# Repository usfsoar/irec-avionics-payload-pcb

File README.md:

# IREC Avionics Payload PCB

This is the PCB for the payload of USF Society of Aeronautics and Rocketry's 2019 IREC rocket. The PCB is made in KiCad (pronounced key-cad). The different two parts of the payload are split into the folders ***payload_ground_pcb***, the ground station, and ***payload_main_pcb***, the cubesat payload, under those there are the files are:

* ***avionics-\*.pro*** - This is the base project which you should open in KiCad.
* ***avionics-\*.sch*** - This is the sketch of the PCB and shows which components should be connected where.
* ***avionics-\*.kicad_pcb*** - This is the actual PCB that has the components laid out and connected with physical dimensions.
* ***components*** - This folder contains components that are not by default included with KiCad

## About the board

The main components of the Cubesat Payload are:

* [Teensy 4.0](https://www.pjrc.com/store/teensy40.html) - This small Arduino compatible board is very powerful for its size with 600 MHz, 1M RAM, and 2M Flash as well as lots of connectivity options.
* [MS5607](https://www.te.com/commerce/DocumentDelivery/DDEController?Action=showdoc&DocId=Data+Sheet%7FMS5607-02BA03%7FB2%7Fpdf%7FEnglish%7FENG_DS_MS5607-02BA03_B2.pdf%7FCAT-BLPS0035) - This is the barometric sensor for the board, it provides high resolution and low pressure while being inexpensive and having a digital interface.
* [ADIS16470](https://www.analog.com/media/en/technical-documentation/data-sheets/ADIS16470.pdf) - This is the inertial measurement unit  which measures acceleration and direction. This highend component will provide an accurate and precice measurments and is the core of the payloads ability to be tracked in realtime by the ground station.
* [SAM M8Q](https://www.u-blox.com/sites/default/files/SAM-M8Q_DataSheet_%28UBX-16012619%29.pdf) - This is the GPS module and it provides a built in antenna and a digital interface.
* [RFM95W](https://cdn.sparkfun.com/assets/learn_tutorials/8/0/4/RFM95_96_97_98W.pdf) - For now this is a temporary RF module that will stand in for what ever RF solution is decided while testing. It provides many benefits for this purpose such as being in the 915MHz range and having long enough range that if necessary it could be used for launch.

The main components of the Ground Station are:

* Teensy 4.0
* SAM M8Q
* RFM95W

## How to contribute

KiCad is a free and open source software that is available on most desktop OSs. To learn how to use KiCad [here](https://github.com/MalphasWats/hawk) is a pretty great tutorial that goes through making a simple PCB. You can go at your own pace but it should take about an hour but after that you should have a pretty good understanding of KiCad.

If you want to add-on to the board the best way would be to create a hierarchical sheet if you are adding on a new subsystem or if you are adjusting the main board try not to adjust (move, rename, etc) items that you do not plan to change.

If you haven't used Git or GitHub before (or you have and just want the commands to make a pull request for this repository) go [here](https://github.com/usfsoar/irec-avionics-payload-pcb/blob/master/git_instructions.md).

## Pictures

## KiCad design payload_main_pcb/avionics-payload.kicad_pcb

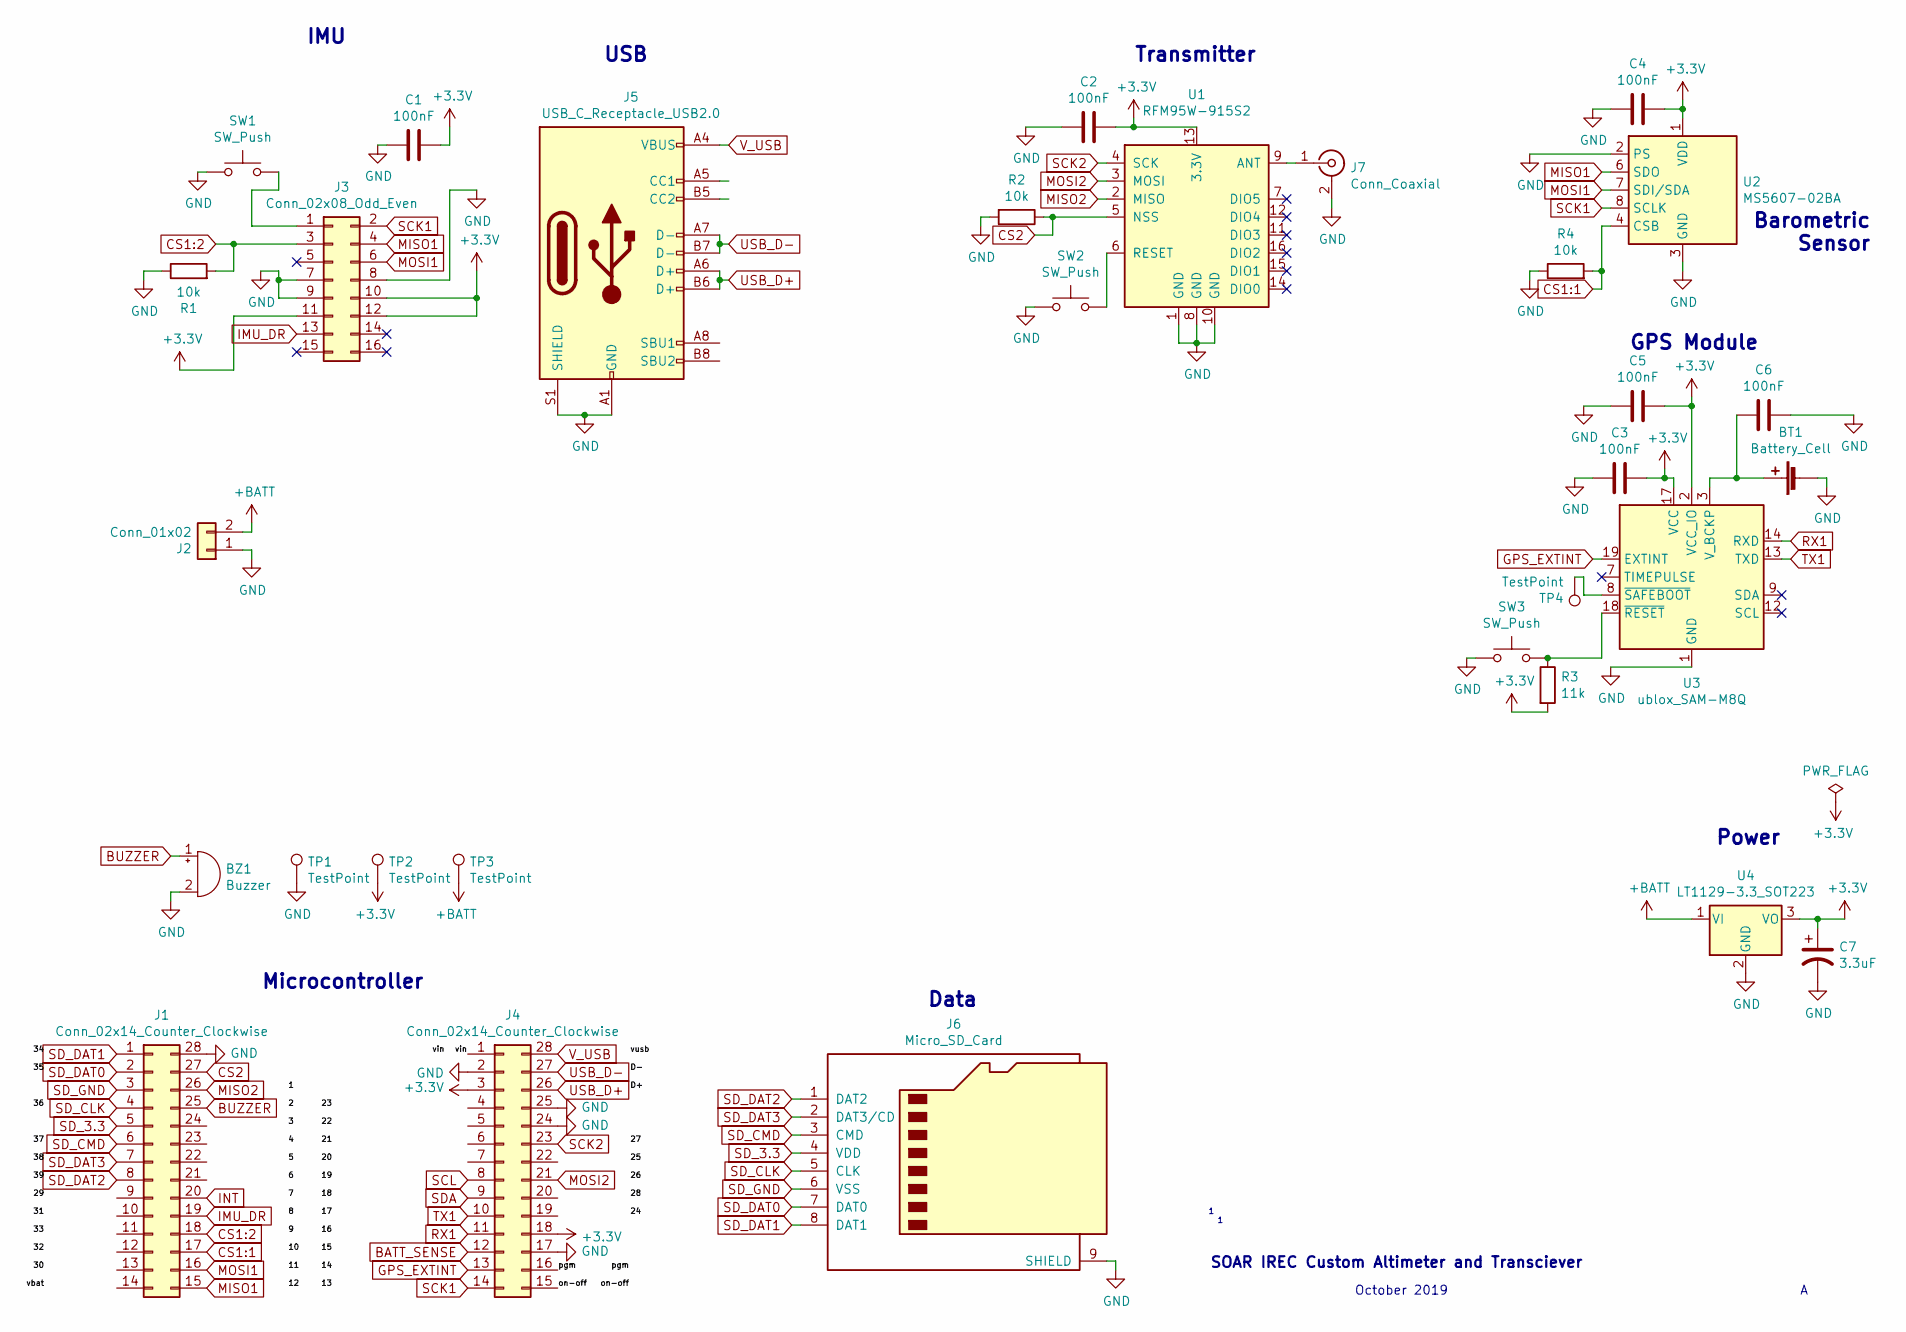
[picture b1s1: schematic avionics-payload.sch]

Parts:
BT1: Battery_Cell; BatteryHolder_Keystone_1060_1x2032
BZ1: Buzzer; Buzzer_CUI_CPT-9019S-SMT
C1, C2, C3, C4, C5, C6: 100nF; C_1206_3216Metric_Pad1.42x1.75mm_HandSolder
C7: 3.3uF; CP_Elec_4x3.9
J1, J4: Conn_02x14_Counter_Clockwise; PinSocket_2x14_P2.54mm_Vertical
J2: Conn_01x02; TerminalBlock_bornier-2_P5.08mm
J3: Conn_02x08_Odd_Even; PinHeader_2x08_P2.00mm_Vertical_SMD
J5: USB_C_Receptacle_USB2.0; USB_C_Receptacle_GCT_USB4085
J6: Micro_SD_Card; microSD_HC_Wuerth_693072010801
J7: Conn_Coaxial; SMA_Amphenol_132291_Vertical
R1, R2, R4: 10k; R_1206_3216Metric_Pad1.42x1.75mm_HandSolder
R3: 11k; R_1206_3216Metric_Pad1.42x1.75mm_HandSolder
SW1, SW2, SW3: SW_Push; SW_SPST_FSMSM
TP1, TP2, TP3: TestPoint; TestPoint_Loop_D2.50mm_Drill1.0mm
TP4: TestPoint; Pin_D1.0mm_L10.0mm
U1: RFM95W-915S2; HOPERF_RFM9XW_SMD
U2: MS5607-02BA; LGA-8_3x5mm_P1.25mm
U3: ublox_SAM-M8Q
U4: LT1129-3.3_SOT223; SOT-223-3_TabPin2

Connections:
+3V3: C1.1, C2.1, C3.1, C4.1, C5.1, C7.1, J3.10, J3.11, J3.12, J4.3, J4.18, R3.2, TP2.1, U1.13 (3.3V), U2.1 (VDD), U3.2 (VCC_IO), U3.17 (VCC), U4.3 (VO)
+BATT: J2.2, TP3.1, U4.1 (VI)
/on-off: J4.15
/pgm: J4.16
/vin: J4.1
BATT_SENSE: J4.12
BUZZER: BZ1.1 (-), J1.25
CS1:1: J1.17, R4.2, U2.4 (CSB), U2.5 (CSB)
CS1:2: J1.18, J3.3, R1.2
CS2: J1.27, R2.1, U1.5 (NSS)
GND: BT1.2 (-), BZ1.2 (+), C1.2, C2.2, C3.2, C4.2, C5.2, C6.1, C7.2, J1.28, J2.1, J3.7, J3.8, J3.9, J4.2, J4.17, J4.24, J4.25, J5.A1 (GND), J5.A12 (GND), J5.B1 (GND), J5.B12 (GND), J5.S1 (SHIELD), J6.9 (SHIELD), J7.2 (Ext), R1.1, R2.2, R4.1, SW1.1, SW2.1, SW3.1, TP1.1, U1.1 (GND), U1.8 (GND), U1.10 (GND), U2.2 (PS), U2.3 (GND), U3.1 (GND), U3.4 (GND), U3.5 (GND), U3.6 (GND), U3.10 (GND), U3.11 (GND), U3.15 (GND), U3.16 (GND), U3.20 (GND), U4.2 (GND)
GPS_EXTINT: J4.13, U3.19 (EXTINT)
IMU_DR: J1.19, J3.13
INT: J1.20
MISO1: J1.15, J3.4, U2.6 (SDO)
MISO2: J1.26, U1.2 (MISO)
MOSI1: J1.16, J3.6, U2.7 (SDI/SDA)
MOSI2: J4.21, U1.3 (MOSI)
unnamed: BT1.1 (+), C6.2, U3.3 (V_BCKP)
unnamed: J3.1, SW1.2
unnamed: J7.1 (In), U1.9 (ANT)
unnamed: R3.1, SW3.2, U3.18 (~RESET)
unnamed: SW2.2, U1.6 (RESET)
unnamed: TP4.1, U3.8 (~SAFEBOOT)
RX1: J4.11, U3.14 (RXD)
SCK1: J3.2, J4.14, U2.8 (SCLK)
SCK2: J4.23, U1.4 (SCK)
SCL: J4.8
SDA: J4.9
SD_3.3: J1.5, J6.4 (VDD)
SD_CLK: J1.4, J6.5 (CLK)
SD_CMD: J1.6, J6.3 (CMD)
SD_DAT0: J1.2, J6.7 (DAT0)
SD_DAT1: J1.1, J6.8 (DAT1)
SD_DAT2: J1.8, J6.1 (DAT2)
SD_DAT3: J1.7, J6.2 (DAT3/CD)
SD_GND: J1.3, J6.6 (VSS)
TX1: J4.10, U3.13 (TXD)
USB_D+: J4.26, J5.A6 (D+), J5.B6 (D+)
USB_D-: J4.27, J5.A7 (D-), J5.B7 (D-)
V_USB: J4.28, J5.A4 (VBUS), J5.A9 (VBUS), J5.B4 (VBUS), J5.B9 (VBUS)

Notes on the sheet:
SOAR IREC Custom Altimeter and Transciever
October 2019
Transmitter
GPS Module
Power
Barometric Sensor
Data
IMU
USB
Microcontroller

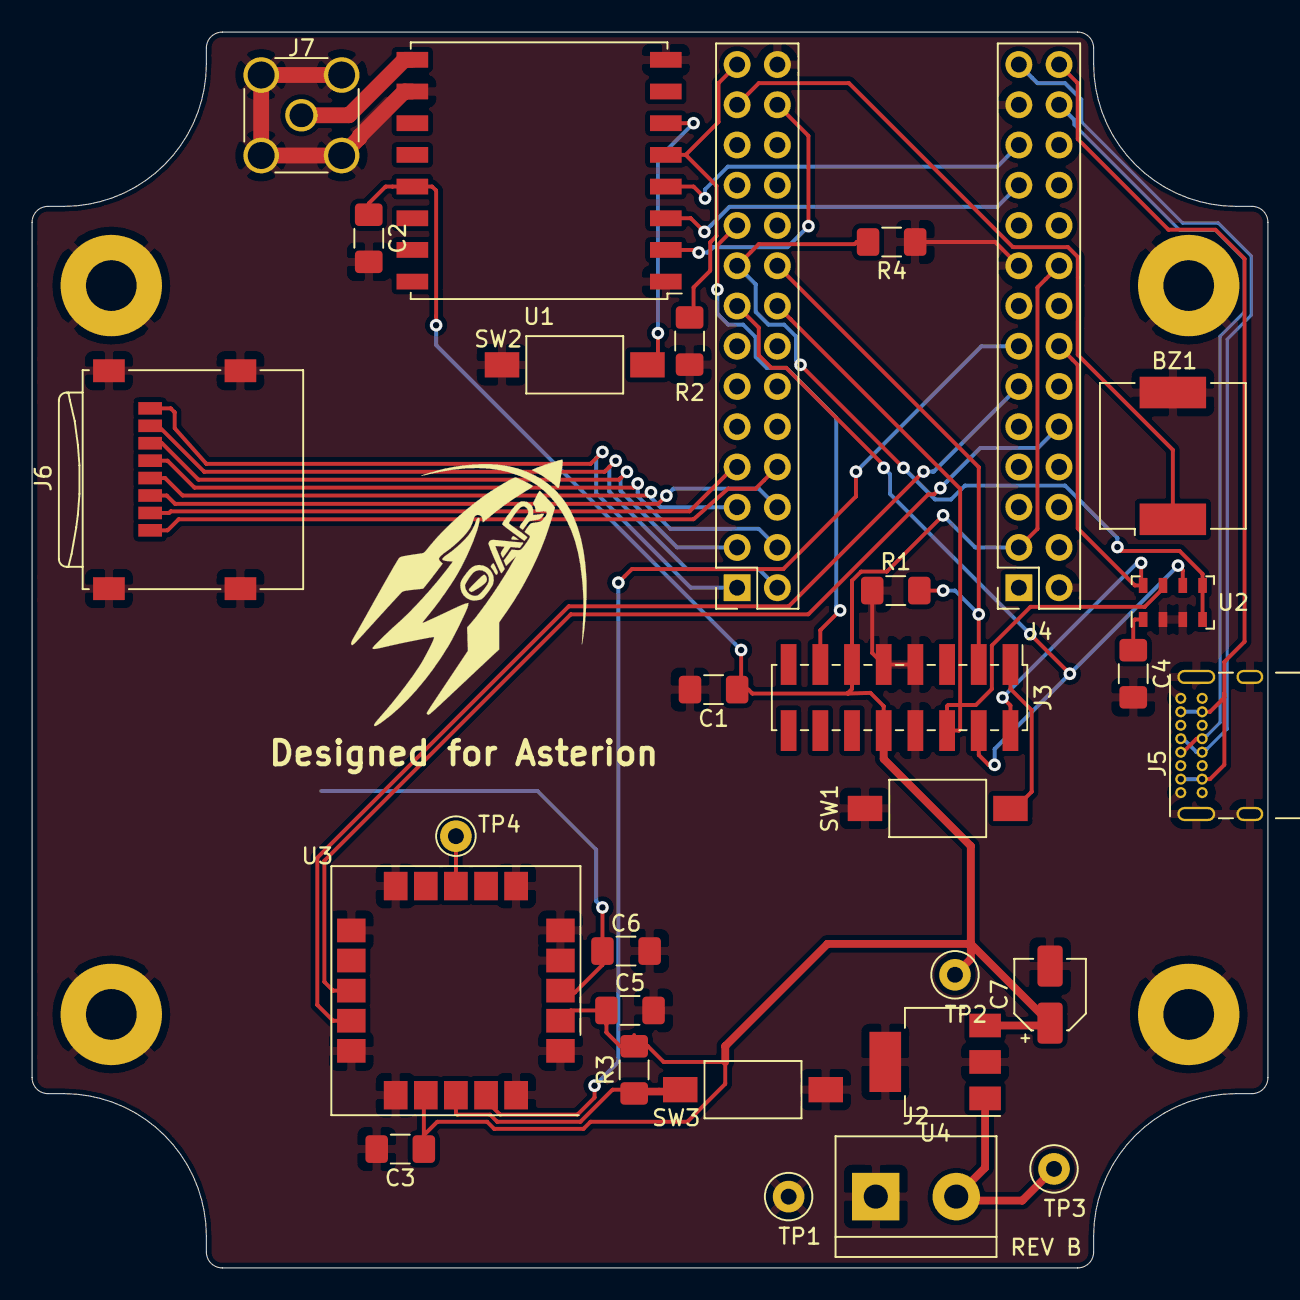
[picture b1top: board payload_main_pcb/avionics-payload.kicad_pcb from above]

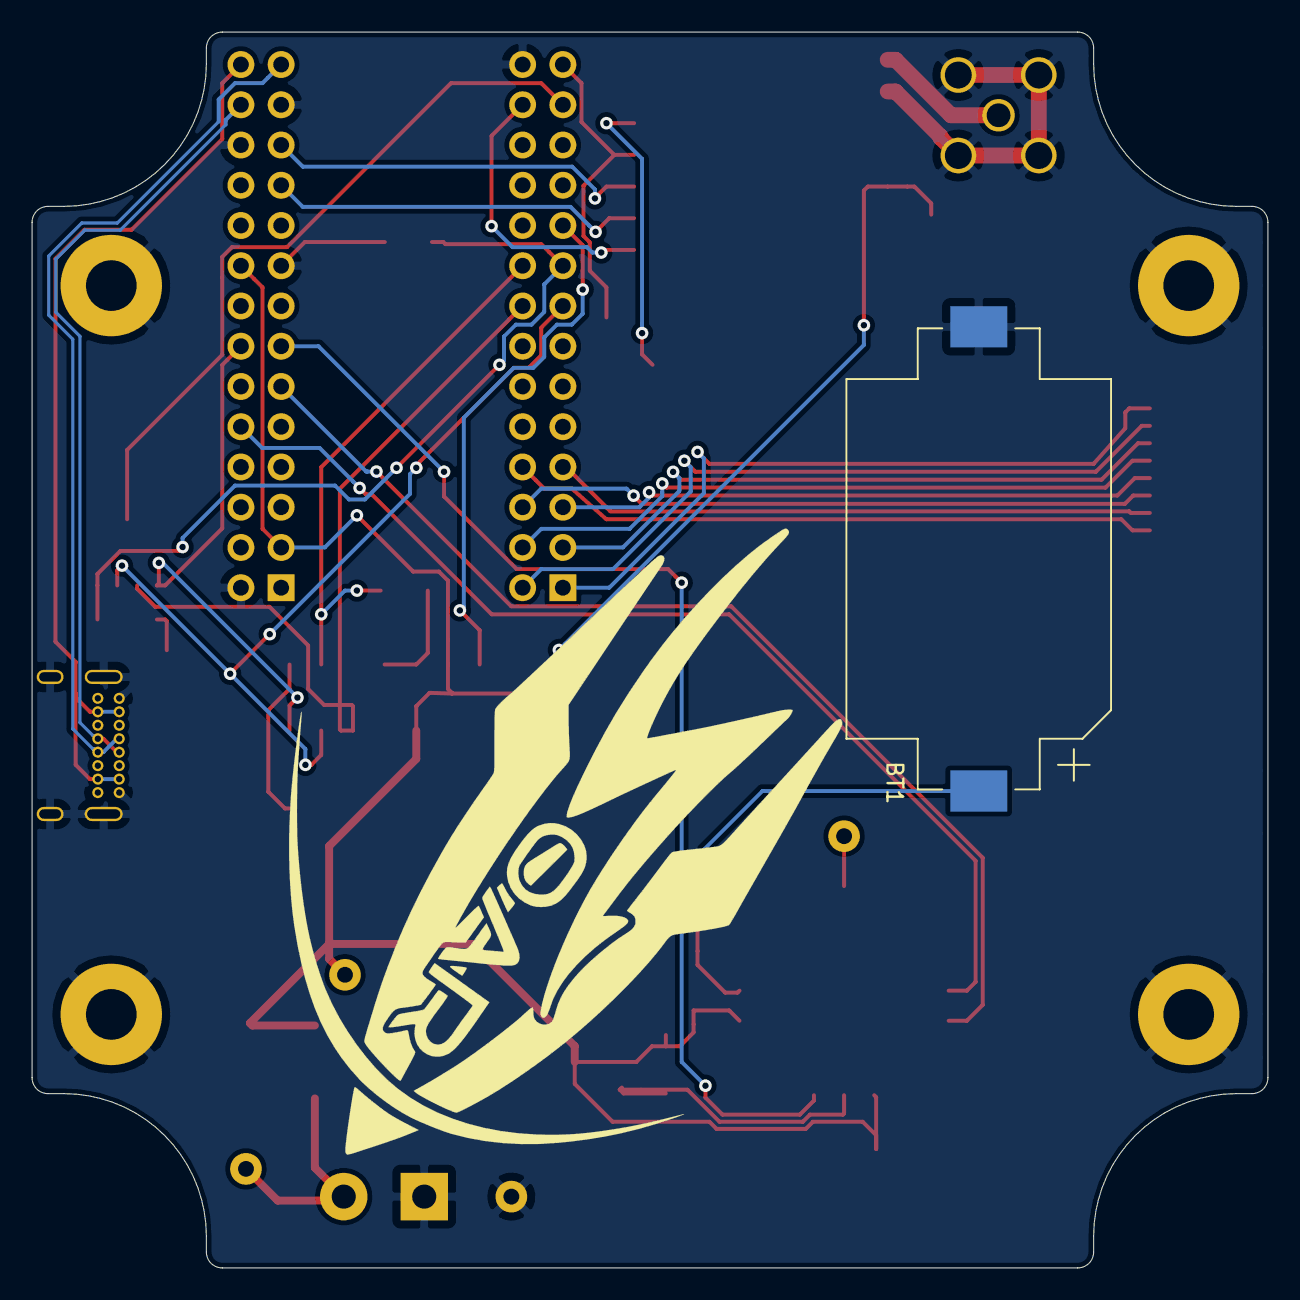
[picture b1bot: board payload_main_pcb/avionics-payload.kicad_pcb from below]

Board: 2 copper layers, 78.0 x 78.0 mm, 33 parts (2 on the bottom side), 34 nets.

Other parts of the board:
Ref**: Val**; drawing
Ref**#2: Val**; logo

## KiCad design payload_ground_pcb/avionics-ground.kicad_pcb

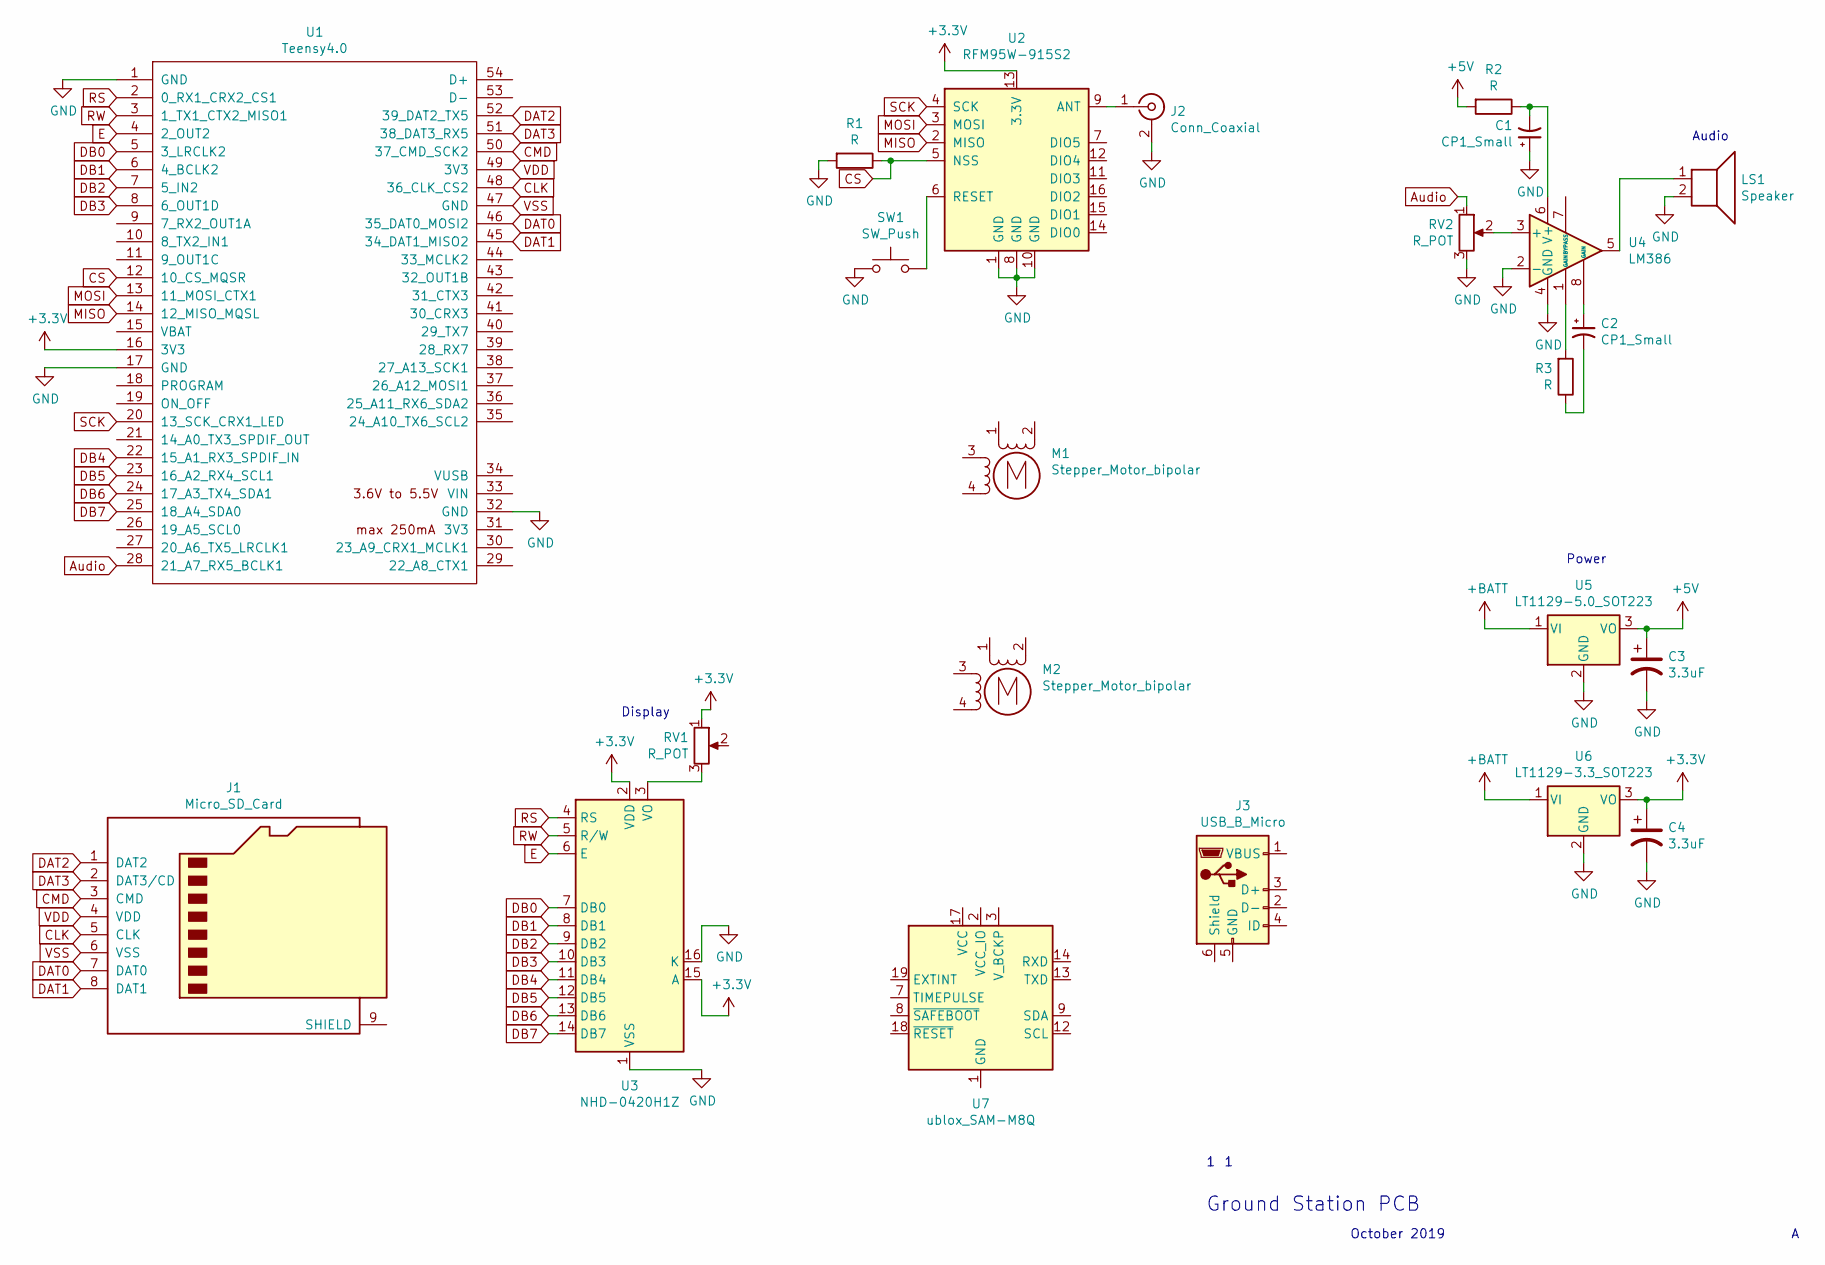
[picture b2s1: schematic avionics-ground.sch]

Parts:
C1, C2: CP1_Small; CP_EIA-1608-08_AVX-J_Pad1.25x1.05mm_HandSolder
C3, C4: 3.3uF; CP_EIA-1608-08_AVX-J_Pad1.25x1.05mm_HandSolder
J1: Micro_SD_Card; microSD_HC_Wuerth_693072010801
J2: Conn_Coaxial; SMA_Amphenol_132134-14_Vertical
J3: USB_B_Micro; USB_Mini-B_Lumberg_2486_01_Horizontal
LS1: Speaker; Buzzer_Murata_PKMCS0909E4000-R1
M1, M2: Stepper_Motor_bipolar
R1, R2, R3: R; R_0805_2012Metric_Pad1.15x1.40mm_HandSolder
RV1, RV2: R_POT; Potentiometer_ACP_CA6-VSMD_Vertical_Hole
SW1: SW_Push; SW_PUSH_6mm
U1: Teensy4.0; Teensy40
U2: RFM95W-915S2; HOPERF_RFM9XW_SMD
U3: NHD-0420H1Z
U4: LM386; DIP-8_W7.62mm_SMDSocket_SmallPads
U5: LT1129-5.0_SOT223; SOT-223-3_TabPin2
U6: LT1129-3.3_SOT223; SOT-223-3_TabPin2
U7: ublox_SAM-M8Q

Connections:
+3V3: C4.1, RV1.1, U1.16 (3V3), U2.13 (3.3V), U3.2 (VDD), U3.15 (A), U6.3 (VO)
+5V: C3.1, R2.2, U5.3 (VO)
+BATT: U5.1 (VI), U6.1 (VI)
Audio: RV2.1, U1.28 (21_A7_RX5_BCLK1)
CLK: J1.5 (CLK), U1.48 (36_CLK_CS2)
CMD: J1.3 (CMD), U1.50 (37_CMD_SCK2)
CS: R1.1, U1.12 (10_CS_MQSR), U2.5 (NSS)
DAT0: J1.7 (DAT0), U1.46 (35_DAT0_MOSI2)
DAT1: J1.8 (DAT1), U1.45 (34_DAT1_MISO2)
DAT2: J1.1 (DAT2), U1.52 (39_DAT2_TX5)
DAT3: J1.2 (DAT3/CD), U1.51 (38_DAT3_RX5)
DB0: U1.5 (3_LRCLK2), U3.7 (DB0)
DB1: U1.6 (4_BCLK2), U3.8 (DB1)
DB2: U1.7 (5_IN2), U3.9 (DB2)
DB3: U1.8 (6_OUT1D), U3.10 (DB3)
DB4: U1.22 (15_A1_RX3_SPDIF_IN), U3.11 (DB4)
DB5: U1.23 (16_A2_RX4_SCL1), U3.12 (DB5)
DB6: U1.24 (17_A3_TX4_SDA1), U3.13 (DB6)
DB7: U1.25 (18_A4_SDA0), U3.14 (DB7)
E: U1.4 (2_OUT2), U3.6 (E)
GND: C1.1, C3.2, C4.2, J2.2 (Ext), LS1.2, R1.2, RV2.3, SW1.1, U1.1 (GND), U1.17 (GND), U1.32 (GND), U2.1 (GND), U2.8 (GND), U2.10 (GND), U3.1 (VSS), U3.16 (K), U4.2 (-), U4.4 (GND), U5.2 (GND), U6.2 (GND)
MISO: U1.14 (12_MISO_MQSL), U2.2 (MISO)
MOSI: U1.13 (11_MOSI_CTX1), U2.3 (MOSI)
unnamed: C1.2, R2.1, U4.6 (V+)
unnamed: C2.1, U4.8 (GAIN)
unnamed: C2.2, R3.1
unnamed: J2.1 (In), U2.9 (ANT)
unnamed: LS1.1, U4.5
unnamed: R3.2, U4.1 (GAIN)
unnamed: RV1.3, U3.3 (VO)
unnamed: RV2.2, U4.3 (+)
unnamed: SW1.2, U2.6 (RESET)
unnamed: U7.1 (GND), U7.4 (GND), U7.5 (GND), U7.6 (GND), U7.10 (GND), U7.11 (GND), U7.15 (GND), U7.16 (GND), U7.20 (GND)
RS: U1.2 (0_RX1_CRX2_CS1), U3.4 (RS)
RW: U1.3 (1_TX1_CTX2_MISO1), U3.5 (R/W)
SCK: U1.20 (13_SCK_CRX1_LED), U2.4 (SCK)
VDD: J1.4 (VDD), U1.49 (3V3)
VSS: J1.6 (VSS), U1.47 (GND)

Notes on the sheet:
Power
Audio
Ground Station PCB
October 2019
Display

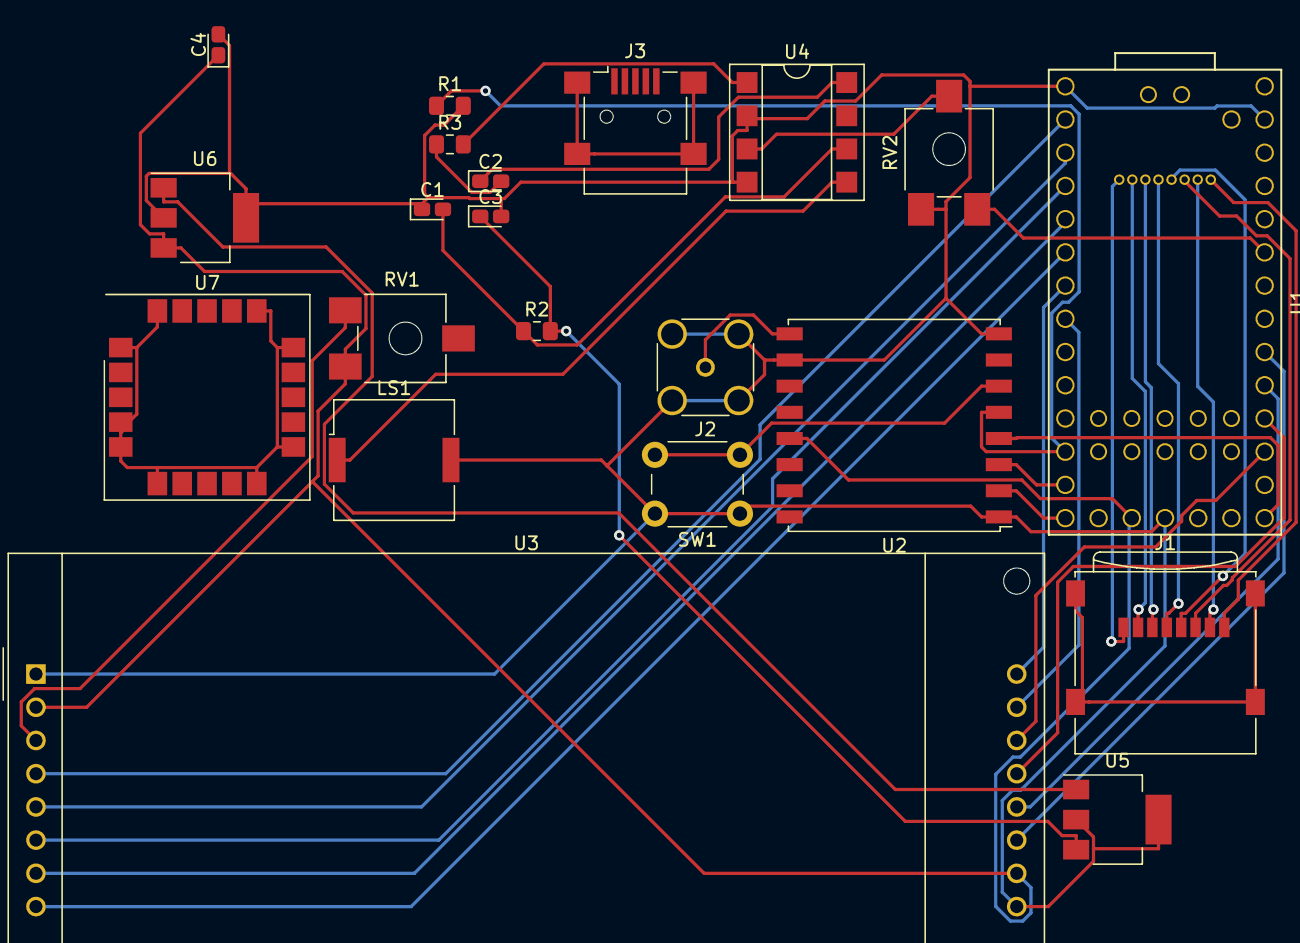
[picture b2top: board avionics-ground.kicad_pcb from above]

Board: 2 copper layers, 21 parts (0 on the bottom side), 38 nets.

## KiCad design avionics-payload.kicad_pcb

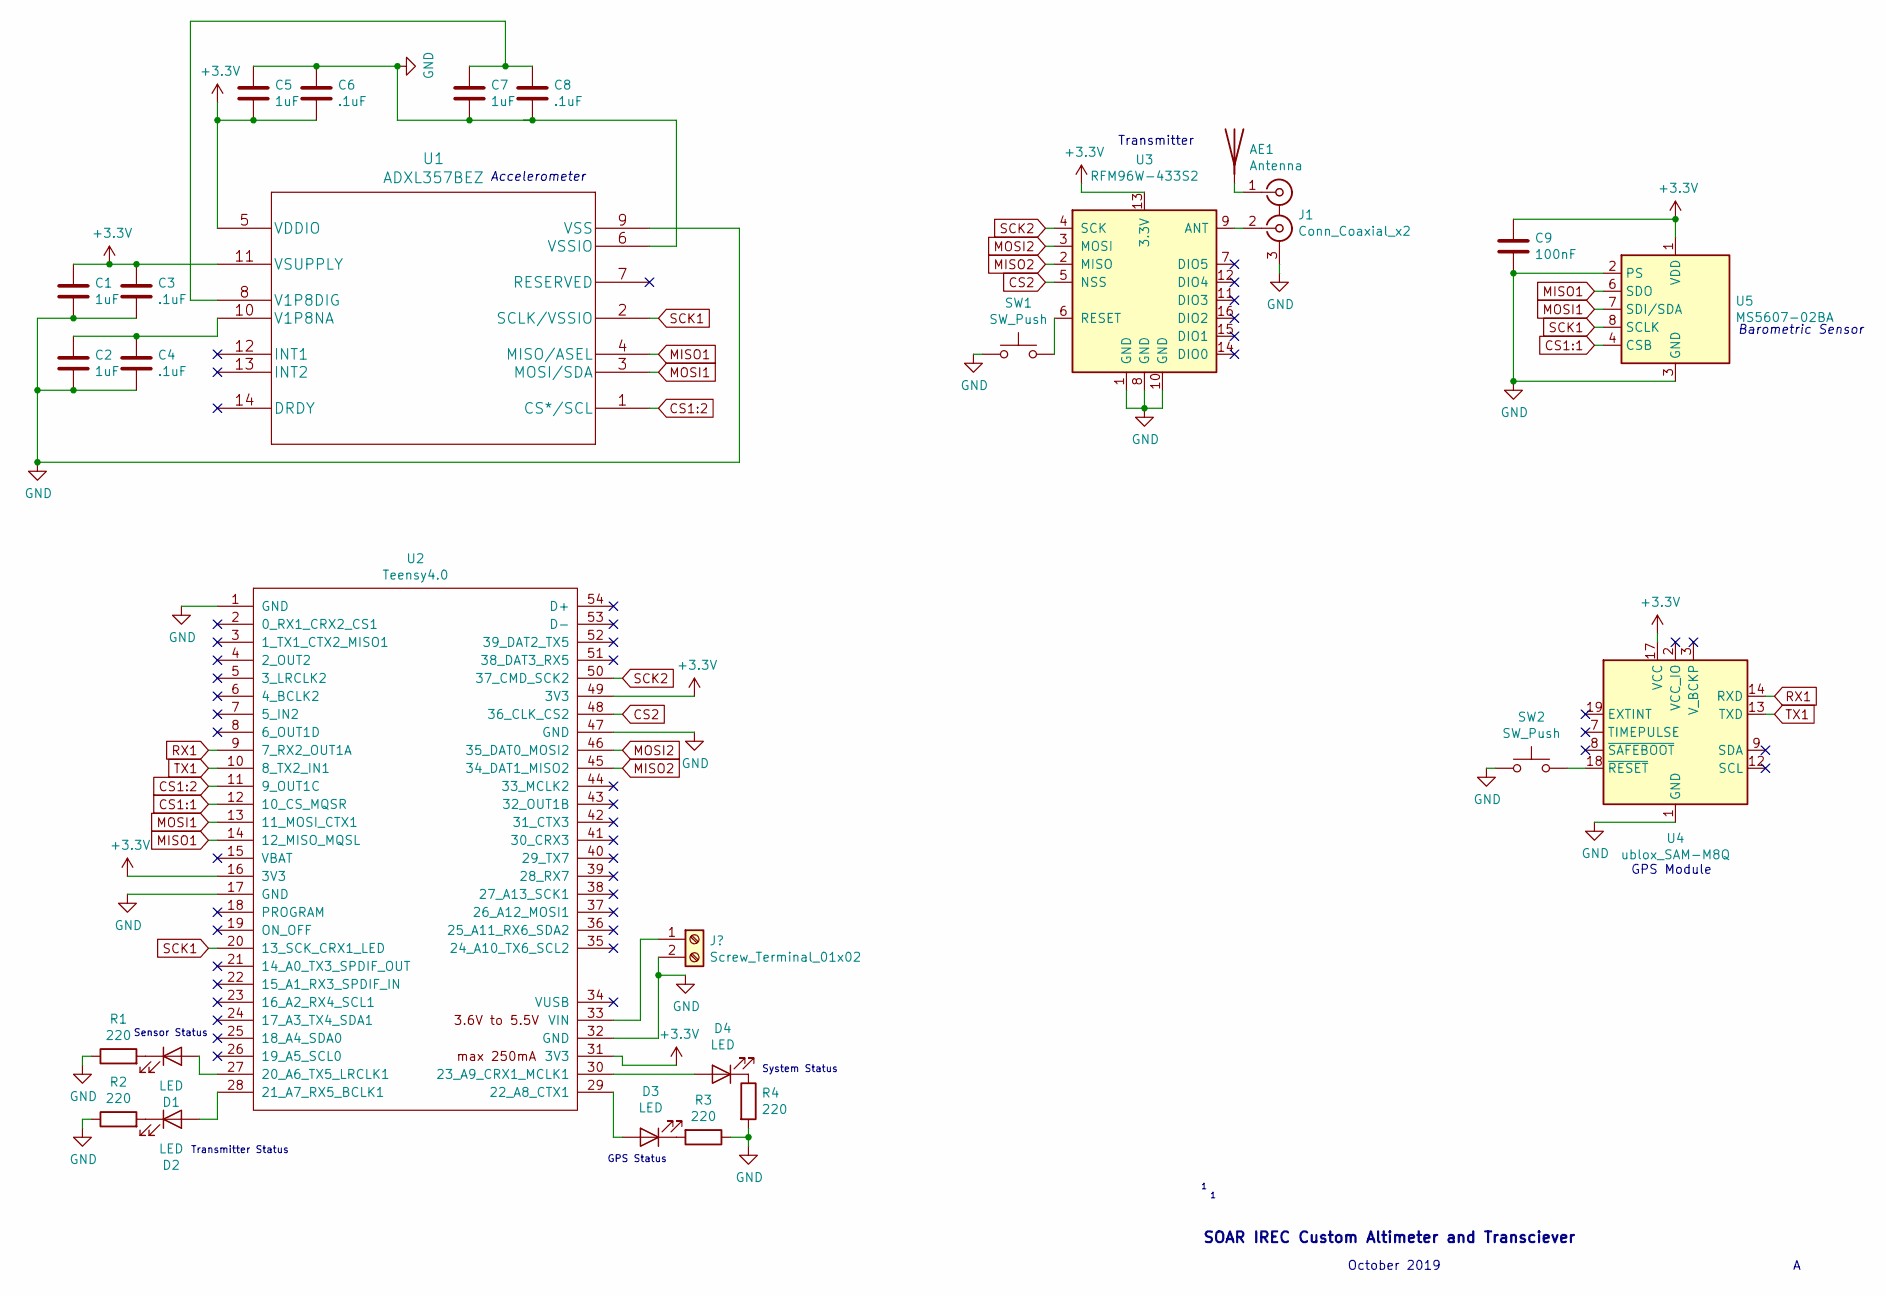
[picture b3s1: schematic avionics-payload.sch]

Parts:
AE1: Antenna
C1, C2, C5, C7: 1uF; C_0805_2012Metric_Pad1.15x1.40mm_HandSolder
C3, C4, C6, C8: .1uF; C_0805_2012Metric_Pad1.15x1.40mm_HandSolder
C9: 100nF; C_0805_2012Metric_Pad1.15x1.40mm_HandSolder
D1, D2, D3, D4: LED; LED_1206_3216Metric_Pad1.42x1.75mm_HandSolder
J1: Conn_Coaxial_x2; SMA_Amphenol_132134-14_Vertical
R1, R2, R3, R4: 220; R_0805_2012Metric_Pad1.15x1.40mm_HandSolder
SW1, SW2: SW_Push; SW_PUSH_6mm
U1: ADXL357BEZ
U2: Teensy4.0; Teensy40
U3: RFM96W-433S2; HOPERF_RFM9XW_SMD
U4: ublox_SAM-M8Q
U5: MS5607-02BA; LGA-8_3x5mm_P1.25mm

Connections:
+3V3: C1.1, C3.1, C5.2, C6.2, C9.1, U1.5 (VDDIO), U1.11 (VSUPPLY), U2.16 (3V3), U2.31 (3V3), U2.49 (3V3), U3.13 (3.3V), U4.17 (VCC), U5.1 (VDD)
CS1:1: U2.12 (10_CS_MQSR), U5.4 (CSB), U5.5 (CSB)
CS1:2: U1.1 (CS*/SCL), U2.11 (9_OUT1C)
CS2: U2.48 (36_CLK_CS2), U3.5 (NSS)
GND: C1.2, C2.2, C3.2, C4.2, C5.1, C6.1, C7.2, C8.2, C9.2, J1.3 (EXT), R1.1, R2.1, R3.1, R4.2, SW1.1, SW2.1, U1.6 (VSSIO), U1.9 (VSS), U2.1 (GND), U2.17 (GND), U2.32 (GND), U2.47 (GND), U3.1 (GND), U3.8 (GND), U3.10 (GND), U4.1 (GND), U4.4 (GND), U4.5 (GND), U4.6 (GND), U4.10 (GND), U4.11 (GND), U4.15 (GND), U4.16 (GND), U4.20 (GND), U5.2 (PS), U5.3 (GND)
MISO1: U1.4 (MISO/ASEL), U2.14 (12_MISO_MQSL), U5.6 (SDO)
MISO2: U2.45 (34_DAT1_MISO2), U3.2 (MISO)
MOSI1: U1.3 (MOSI/SDA), U2.13 (11_MOSI_CTX1), U5.7 (SDI/SDA)
MOSI2: U2.46 (35_DAT0_MOSI2), U3.3 (MOSI)
unnamed: AE1.1, J1.1 (IN1)
unnamed: C2.1, C4.1, U1.10 (V1P8NA)
unnamed: C7.1, C8.1, U1.8 (V1P8DIG)
unnamed: D1.1 (K), R1.2
unnamed: D1.2 (A), U2.27 (20_A6_TX5_LRCLK1)
unnamed: D2.1 (K), R2.2
unnamed: D2.2 (A), U2.28 (21_A7_RX5_BCLK1)
unnamed: D3.1 (K), R3.2
unnamed: D3.2 (A), U2.29 (22_A8_CTX1)
unnamed: D4.1 (K), R4.1
unnamed: D4.2 (A), U2.30 (23_A9_CRX1_MCLK1)
unnamed: J1.2 (IN2), U3.9 (ANT)
unnamed: SW1.2, U3.6 (RESET)
unnamed: SW2.2, U4.18 (~RESET)
RX1: U2.9 (7_RX2_OUT1A), U4.14 (RXD)
SCK1: U1.2 (SCLK/VSSIO), U2.20 (13_SCK_CRX1_LED), U5.8 (SCLK)
SCK2: U2.50 (37_CMD_SCK2), U3.4 (SCK)
TX1: U2.10 (8_TX2_IN1), U4.13 (TXD)

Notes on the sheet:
SOAR IREC Custom Altimeter and Transciever
October 2019
Barometric Sensor
Transmitter
GPS Module
System Status
Transmitter Status
Sensor Status
GPS Status
Accelerometer

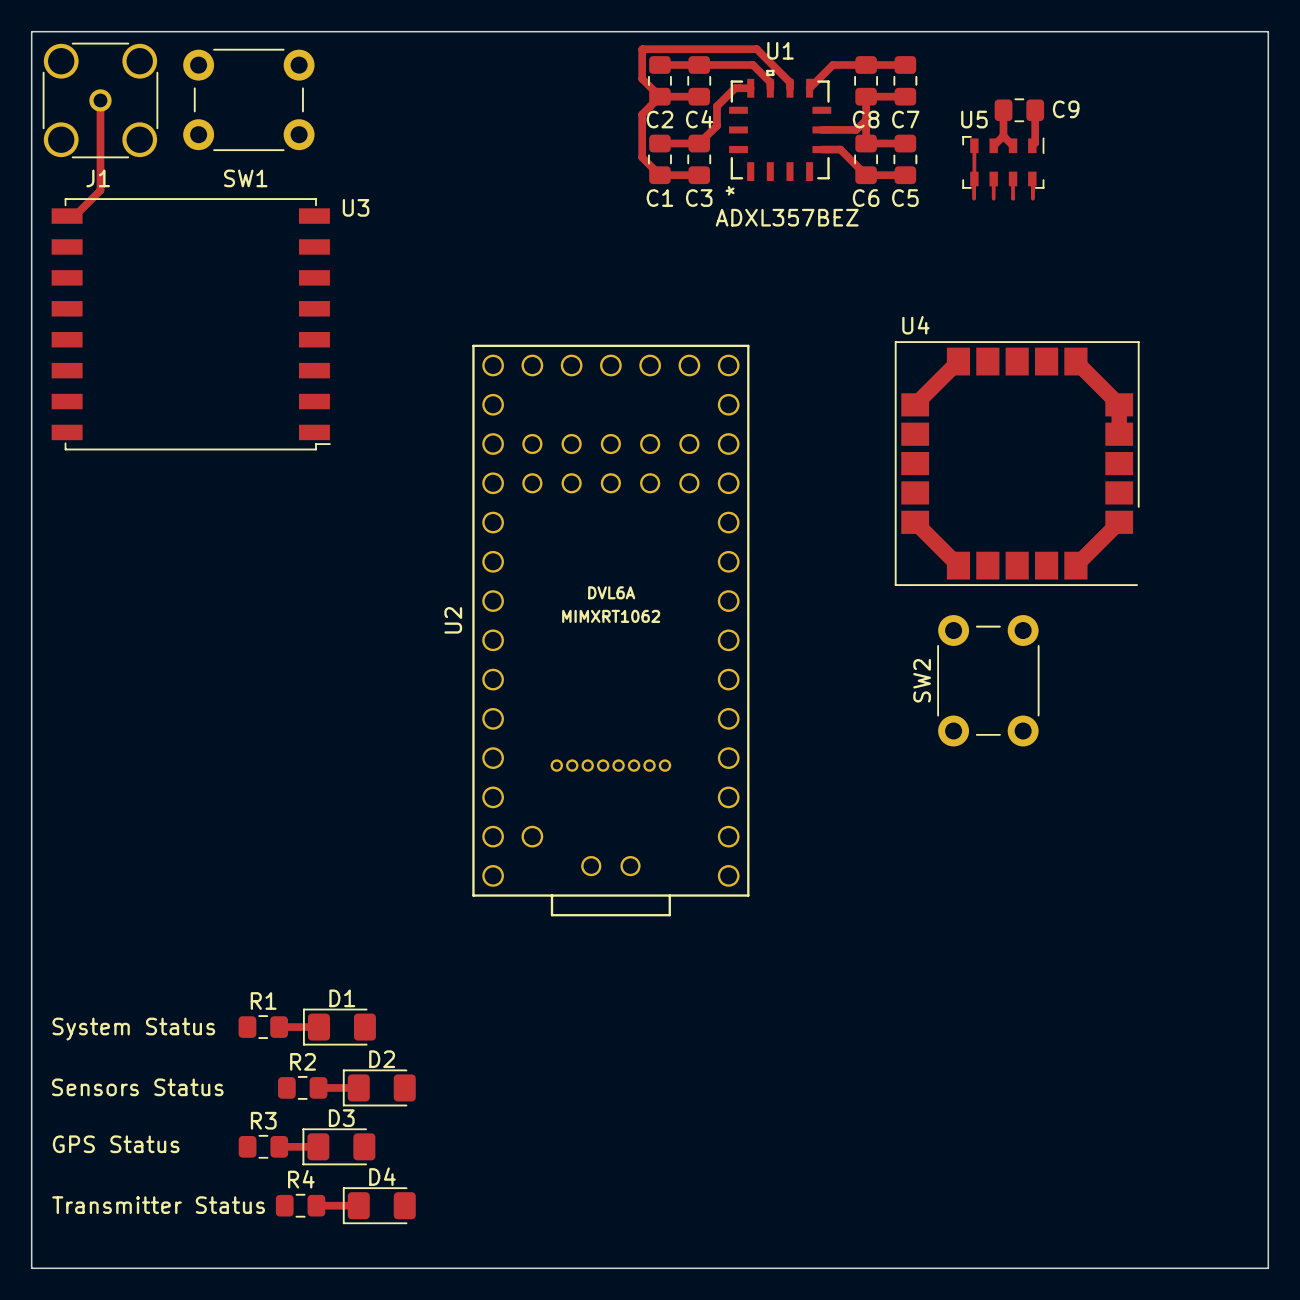
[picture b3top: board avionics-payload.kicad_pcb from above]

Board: 2 copper layers, 80.0 x 80.0 mm, 25 parts (0 on the bottom side), 26 nets.

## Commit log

2019-10-11 Fixed README with tutorial info
2019-10-11 Added links to KiCad site
2019-10-11 Added description of components and images
2019-10-11 Added more on how to get using KiCad
2019-10-12 Added power module and made schematic more modular.
2019-10-13 Moved files to folders and started ground station
2019-10-13 Added SD card
2019-10-15 Work on ground station and new IMU added to payload
2019-10-16 Added data module
2019-10-17 Added logo to board
2019-11-06 Wired boards using autorouter
2019-11-06 Updated .gitignore
2019-11-06 Fixed last commit
2019-11-15 Formatted git_instructions better.
2019-11-15 Integrated ADIS16470 in schematic and removed ADXL357
2019-11-19 Lots of stuff
2019-11-20 Changed buttons and added bottom plane
2019-11-20 Updated pictures
2019-11-20 Updated README with Git info
2019-11-27 PCB REV A
2020-04-02 REV B

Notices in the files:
parts and their libraries:
Copyright 2016 Accelerated Designs. All rights reserved.
